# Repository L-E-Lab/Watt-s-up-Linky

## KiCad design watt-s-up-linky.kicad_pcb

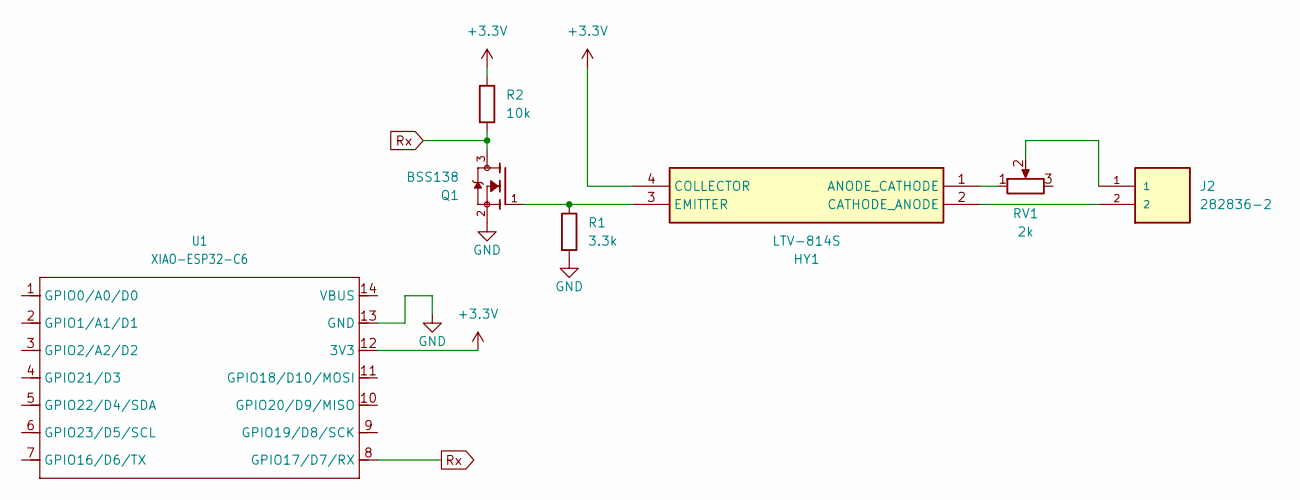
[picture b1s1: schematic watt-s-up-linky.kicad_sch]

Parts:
HY1: LTV-814S; LTV814; Manufacturer_Part_Number LTV-814S; Mouser Part Number 859-LTV-814S
J2: 282836-2; TE_282836-2
Q1: BSS138
R1: 3.3k; R_1206_3216Metric_Pad1.30x1.75mm_HandSolder
R2: 10k; R_1206_3216Metric_Pad1.30x1.75mm_HandSolder
RV1: 2k; Potentiometer_Bourns_3314G_Vertical
U1: XIAO-ESP32-C6; XIAO-ESP32C6-SMD

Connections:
+3.3V: HY1.4 (COLLECTOR), R2.1, U1.12 (3V3)
GND: Q1.2, R1.2, U1.13 (GND)
unnamed: HY1.1 (ANODE_CATHODE), RV1.1
unnamed: HY1.2 (CATHODE_ANODE), J2.2
unnamed: HY1.3 (EMITTER), Q1.1, R1.1
unnamed: J2.1, RV1.2
Rx: Q1.3, R2.2, U1.8 (GPIO17/D7/RX)

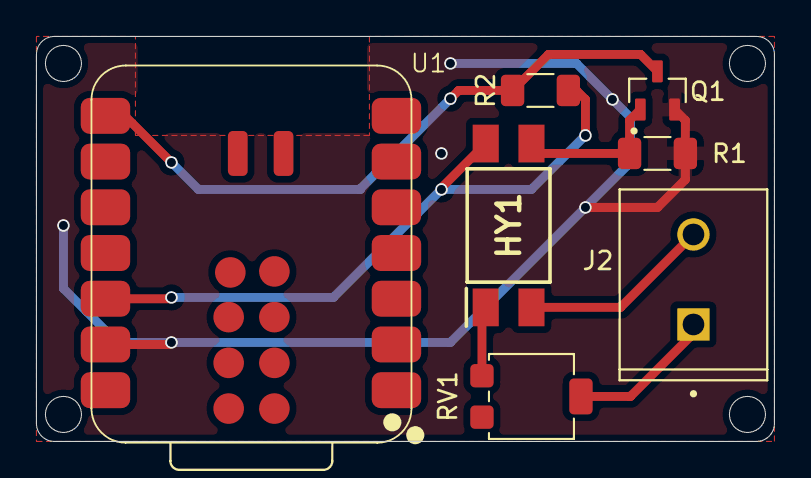
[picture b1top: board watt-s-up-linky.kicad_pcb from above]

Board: 2 copper layers, 41.0 x 22.5 mm, 7 parts (0 on the bottom side), 7 nets.
